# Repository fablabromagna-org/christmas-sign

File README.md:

# christmas-sign
Tre pomeriggi di open lab per realizzare insieme delle decorazioni a LED utilizzando CAD 2D-3D, Stampa 3D a colori, coding Arduino e Circuit Python.

# Circuito di controllo dei led
Il primo disegno KiCad prodotto è nella cartella ATtiny3.

La scelta di utilizzare un ATtiny è legata alla semplicità ed economicità di questa serie di microcontrollori.

L'idea era quella di creare un circuito che:
- potesse essere usato su una breadboard per i primi esperimenti
- fosse alimentabile con un cavo USB-C
- avesse a bordo un regolatore per 3.3v
- portasse fuori tutti i pin del'ATTiny
- avesse a bordo i driver di potenza per pilotare i led direttamente
- potesse essere programmato con un connettore UPDI standard a 6 pin (di cui solo 3 utilizzati)

Molti componenti sono SMD basic che non richiedono quindi una spesa aggiuntiva per il cambio reel sul Pick and place di JLCPCB.

Gli unici componenti extended sono:
- il connettore USB-C
- il regolatore di tensione 3.3v
- la CPU

La prima produzione di 10 schede per un totale di 434 componenti montati in SMD è costata 37 euro comprese VAT e shipping. (avevo un buono sconto di 8,26 euro)

A queste spese bisogna aggiungere le 10 CPU comprate su Mouser a 9,39 che andranno saldate a mano.

JLCPCB infatti non ha a catalogo queste CPU (ATtiny1624)

Fronte

Retro

Schema

Vista 3D

Pdf dello schema **[PDF](ATtiny3/Immagini/Schema.pdf)**.

Così lo volevano loro...

Così lo volevo io...

Ci siamo messi d'accordo.
I diodi erano giusti ma a loro non piacevano.

Quando arriveranno i circuiti montati sapremo chi aveva ragione.

Nel frattempo però, un circuito confermato domenica 3 novembre 2024, va in produzione l'8 novembre, con 5 giorni di ritardo.

Loro chiedono scusa ma la prossima volta lo faccio con PCBWay e vediamo se il maggior costo è giustificato.

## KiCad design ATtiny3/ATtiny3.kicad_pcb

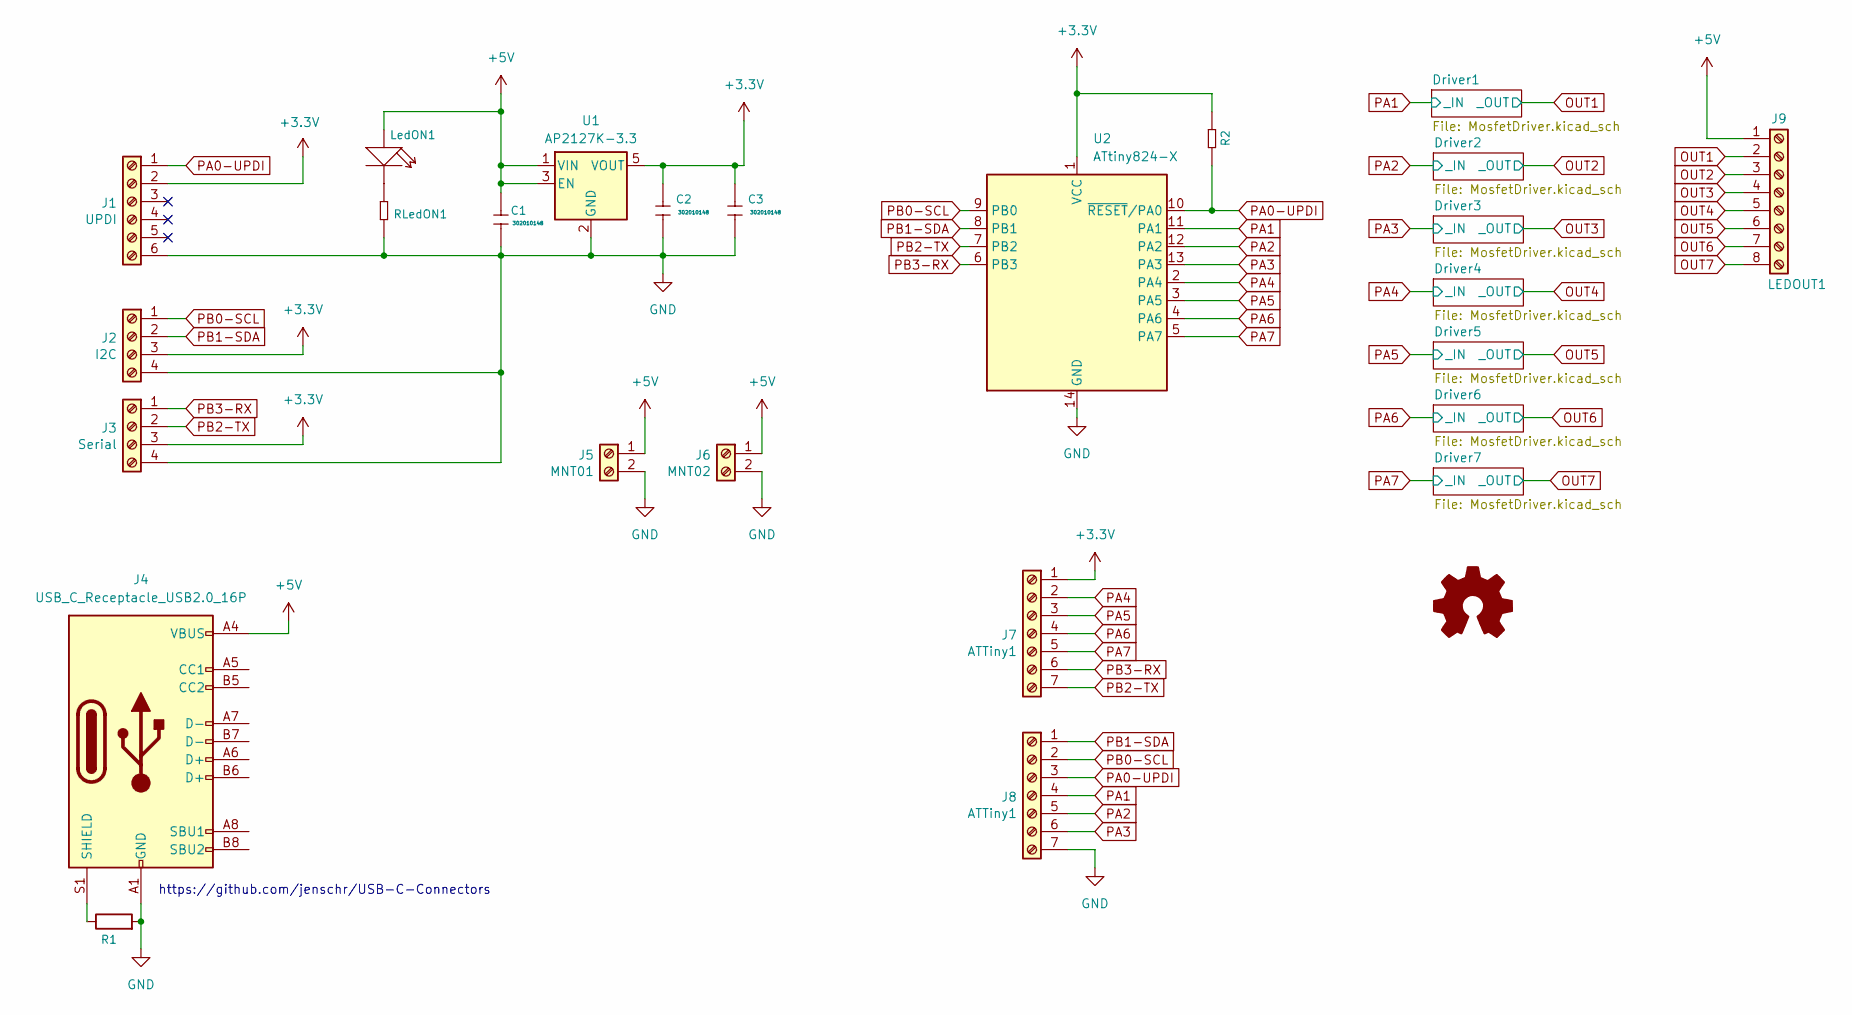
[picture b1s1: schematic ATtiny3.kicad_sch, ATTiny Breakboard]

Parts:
C1, C2, C3: CERAMIC-10UF-10V-10%-X7R_0805_; C_0805_2012Metric; MPN CC0805KKX7R8BB225; LCSC C15850
J1: UPDI; PinHeader_2x03_P2.54mm_Vertical
J2: I2C; PinHeader_1x04_P2.54mm_Vertical
J3: Serial; PinHeader_1x04_P2.54mm_Vertical
J4: USB_C_Receptacle_USB2.0_16P; TYPE-C-31-M-12; LCSC C165948
J5: MNT01; PinHeader_1x02_P2.54mm_Vertical
J6: MNT02; PinHeader_1x02_P2.54mm_Vertical
J7, J8: ATTiny1; PinHeader_1x07_P2.54mm_Vertical
J9: LEDOUT1; PinHeader_1x08_P2.54mm_Vertical
L1: Logo_Open_Hardware_Small; OSHW-Logo_5.7x6mm_SilkScreen
LedON1: SMD-LED-CLEAR-RED_0805_; LED_0805_2012Metric; MPN 17-215SURC_S530-A2_TR8; LCSC C2297
R1: 1M; R_Axial_DIN0204_L3.6mm_D1.6mm_P5.08mm_Horizontal
R2: 10K; R_0805_2012Metric; LCSC C17414
RLedON1: SMD-RES-220R-5%-1_8W_0805_; R_0805_2012Metric; LCSC C17557
U1: AP2127K-3.3; SOT-23-5; LCSC C156285
U2: ATtiny824-X; TSSOP-14_4.4x5mm_P0.65mm; LCSC C3237505

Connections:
+3.3V: C2.1, C3.1, J1.2, J2.3, J3.3, J7.1, R2.1, U1.5 (VOUT), U2.1 (VCC)
+5V: C1.1, J4.A4 (VBUS), J4.A9 (VBUS), J4.B4 (VBUS), J4.B9 (VBUS), J5.1, J6.1, J9.1, LedON1.1 (+), U1.1 (VIN), U1.3 (EN)
GND: C1.2, C2.2, C3.2, J1.6, J2.4, J3.4, J4.A1 (GND), J4.A12 (GND), J4.B1 (GND), J4.B12 (GND), J5.2, J6.2, J8.7, R1.2, RLedON1.2, U1.2 (GND), U2.14 (GND); also elsewhere on the board
unnamed: J4.S1 (SHIELD), R1.1
unnamed: LedON1.2 (-), RLedON1.1
OUT1: J9.2; also elsewhere on the board
OUT2: J9.3; also elsewhere on the board
OUT3: J9.4; also elsewhere on the board
OUT4: J9.5; also elsewhere on the board
OUT5: J9.6; also elsewhere on the board
OUT6: J9.7; also elsewhere on the board
OUT7: J9.8; also elsewhere on the board
PA0-UPDI: J1.1, J8.3, R2.2, U2.10 (~RESET/PA0)
PA1: J8.4, U2.11 (PA1); also elsewhere on the board
PA2: J8.5, U2.12 (PA2); also elsewhere on the board
PA3: J8.6, U2.13 (PA3); also elsewhere on the board
PA4: J7.2, U2.2 (PA4); also elsewhere on the board
PA5: J7.3, U2.3 (PA5); also elsewhere on the board
PA6: J7.4, U2.4 (PA6); also elsewhere on the board
PA7: J7.5, U2.5 (PA7); also elsewhere on the board
PB0-SCL: J2.1, J8.2, U2.9 (PB0)
PB1-SDA: J2.2, J8.1, U2.8 (PB1)
PB2-TX: J3.2, J7.7, U2.7 (PB2)
PB3-RX: J3.1, J7.6, U2.6 (PB3)

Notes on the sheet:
https://github.com/jenschr/USB-C-Connectors

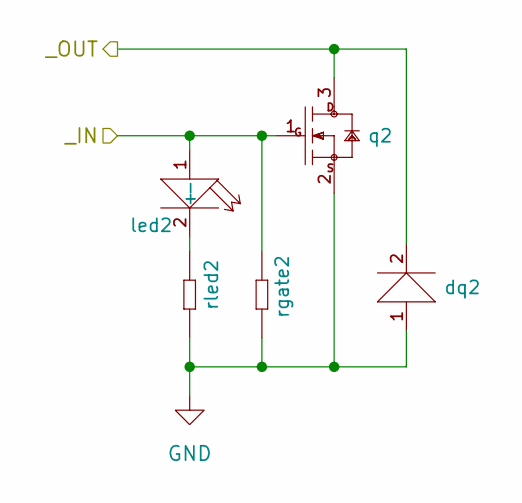
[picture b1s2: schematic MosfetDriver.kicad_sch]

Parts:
dq2: SMD-DIODE-SCHOTTKY-20V-1A_SOD-123_; D_SOD-123; LCSC C8598
led2: SMD-LED-CLEAR-0805; LED_0805_2012Metric; LCSC C2296
q2: SMD-MOSFET-N-CH; SOT-23; LCSC C20917
rgate2: 10K; R_0805_2012Metric; MPN RC0805JR-074K7L; LCSC C17414
rled2: SMD-RES-220R-5%-1_8W_0805_; R_0805_2012Metric; MPN RC0805JR-07220RL; LCSC C17557

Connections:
GND: dq2.1 (+), q2.2 (S), rgate2.2, rled2.2; also elsewhere on the board
unnamed: led2.2 (-), rled2.1
OUT2: dq2.2 (-), q2.3 (D); also elsewhere on the board
PA2: led2.1 (+), q2.1 (G), rgate2.1; also elsewhere on the board

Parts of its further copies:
dq1, dq3, dq4, dq5, dq6, dq7: SMD-DIODE-SCHOTTKY-20V-1A_SOD-123_; D_SOD-123; LCSC C8598
led1, led3, led4, led5, led6, led7: SMD-LED-CLEAR-0805; LED_0805_2012Metric; LCSC C2296
q1, q3, q4, q5, q6, q7: SMD-MOSFET-N-CH; SOT-23; LCSC C20917
rgate1, rgate3, rgate4, rgate5, rgate6, rgate7: 10K; R_0805_2012Metric; MPN RC0805JR-074K7L; LCSC C17414
rled1, rled3, rled4, rled5, rled6, rled7: SMD-RES-220R-5%-1_8W_0805_; R_0805_2012Metric; MPN RC0805JR-07220RL; LCSC C17557

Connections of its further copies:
GND: dq1.1 (+), dq3.1 (+), dq4.1 (+), dq5.1 (+), dq6.1 (+), dq7.1 (+), q1.2 (S), q3.2 (S), q4.2 (S), q5.2 (S), q6.2 (S), q7.2 (S), rgate1.2, rgate3.2, rgate4.2, rgate5.2, rgate6.2, rgate7.2, rled1.2, rled3.2, rled4.2, rled5.2, rled6.2, rled7.2; also elsewhere on the board
unnamed: led1.2 (-), rled1.1
unnamed: led3.2 (-), rled3.1
unnamed: led4.2 (-), rled4.1
unnamed: led5.2 (-), rled5.1
unnamed: led6.2 (-), rled6.1
unnamed: led7.2 (-), rled7.1
OUT1: dq1.2 (-), q1.3 (D); also elsewhere on the board
OUT3: dq3.2 (-), q3.3 (D); also elsewhere on the board
OUT4: dq4.2 (-), q4.3 (D); also elsewhere on the board
OUT5: dq5.2 (-), q5.3 (D); also elsewhere on the board
OUT6: dq6.2 (-), q6.3 (D); also elsewhere on the board
OUT7: dq7.2 (-), q7.3 (D); also elsewhere on the board
PA1: led1.1 (+), q1.1 (G), rgate1.1; also elsewhere on the board
PA3: led3.1 (+), q3.1 (G), rgate3.1; also elsewhere on the board
PA4: led4.1 (+), q4.1 (G), rgate4.1; also elsewhere on the board
PA5: led5.1 (+), q5.1 (G), rgate5.1; also elsewhere on the board
PA6: led6.1 (+), q6.1 (G), rgate6.1; also elsewhere on the board
PA7: led7.1 (+), q7.1 (G), rgate7.1; also elsewhere on the board

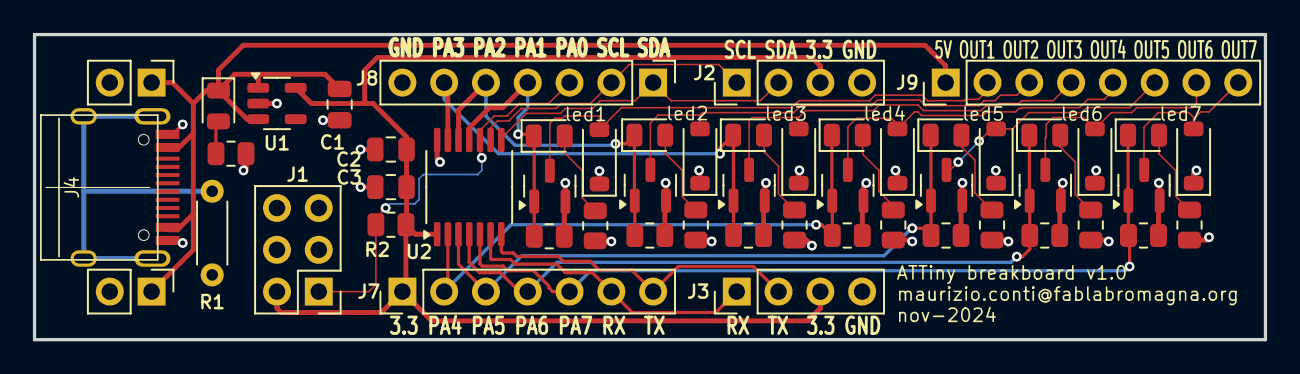
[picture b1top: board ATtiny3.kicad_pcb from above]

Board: 2 copper layers, 74.8 x 18.5 mm, 54 parts (1 on the bottom side), 31 nets.

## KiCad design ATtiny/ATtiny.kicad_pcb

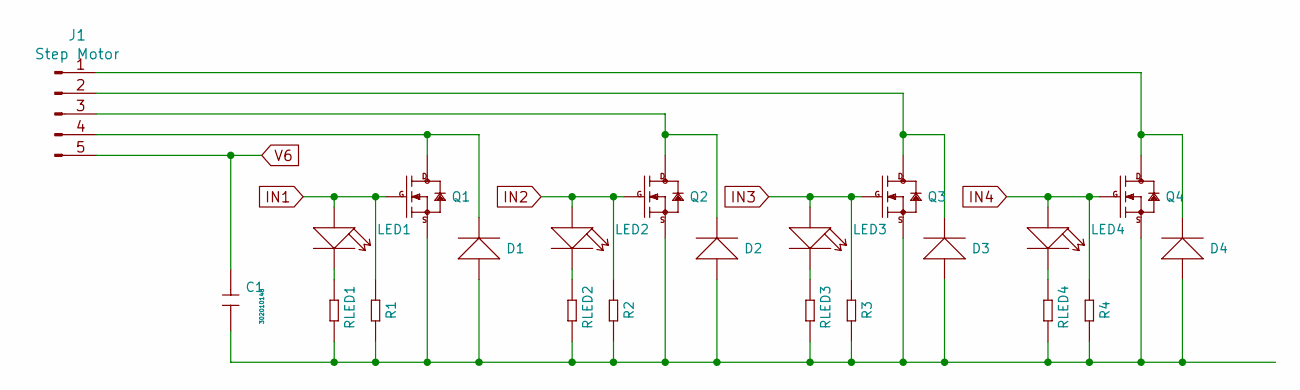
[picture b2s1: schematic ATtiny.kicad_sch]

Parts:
C1: CERAMIC-10UF-10V-10%-X7R_0805_; C_0805_2012Metric; MPN CC0805KKX7R8BB225; LCSC C126586
D1, D2, D3, D4: SMD-DIODE-SCHOTTKY-20V-1A_SOD-123_; D_0805_2012Metric; MPN B5819W; LCSC C84354
J1: Step Motor; JST_EH_B5B-EH-A_1x05_P2.50mm_Vertical
LED1, LED2, LED3, LED4: SMD-LED-CLEAR-RED_0805_; LED-0805; MPN 17-215SURC_S530-A2_TR8; LCSC C2764885
Q1, Q2, Q3, Q4: SMD-MOSFET-N-CH-20V-2.1A-CJ2302_SOT-23_; SOT95P240X115-3N; MPN CJ2302; LCSC C91104
R1, R2, R3, R4: SMD-RES-4.7K-5%-1_8W_0805_; R_0815_2038Metric; MPN RC0805JR-074K7L; LCSC C473295
RLED1, RLED2, RLED3, RLED4: SMD-RES-220R-5%-1_8W_0805_; R_0805_2012Metric; MPN RC0805JR-07220RL; LCSC C365277

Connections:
IN1: LED1.1 (+), Q1.1 (G), R1.1
IN2: LED2.1 (+), Q2.1 (G), R2.1
IN3: LED3.1 (+), Q3.1 (G), R3.1
IN4: LED4.1 (+), Q4.1 (G), R4.1
unnamed: C1.2, D1.1 (+), D2.1 (+), D3.1 (+), D4.1 (+), Q1.2 (S), Q2.2 (S), Q3.2 (S), Q4.2 (S), R1.2, R2.2, R3.2, R4.2, RLED1.2, RLED2.2, RLED3.2, RLED4.2
unnamed: D1.2 (-), J1.4, Q1.3 (D)
unnamed: D2.2 (-), J1.3, Q2.3 (D)
unnamed: D3.2 (-), J1.2, Q3.3 (D)
unnamed: D4.2 (-), J1.1, Q4.3 (D)
unnamed: LED1.2 (-), RLED1.1
unnamed: LED2.2 (-), RLED2.1
unnamed: LED3.2 (-), RLED3.1
unnamed: LED4.2 (-), RLED4.1
V6: C1.1, J1.5

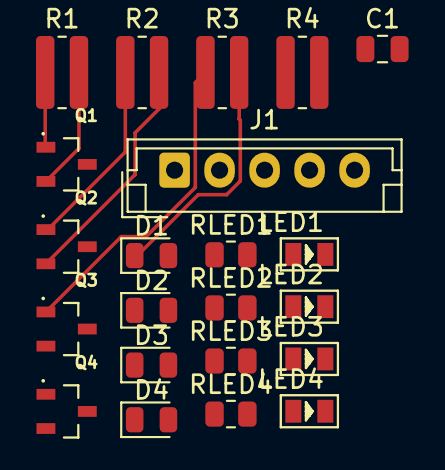
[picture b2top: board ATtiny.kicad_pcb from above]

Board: 2 copper layers, 22 parts (0 on the bottom side), 14 nets.

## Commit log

2024-11-04 Primo ordine JLCPCB
